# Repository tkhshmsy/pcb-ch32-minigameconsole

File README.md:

# PCB-ch32-minigameconsole

Private designed PCB for [CH32V003-GameConsole](https://github.com/wagiminator/CH32V003-GameConsole)

## Features
* Size 45 x 48 mm
  * Panelized 4 pcs in 100 x 100mm
* Using THT parts except CH32V003
  * All parts are able to purchase from [Akizuki-Denshi](https://akizukidenshi.com/)

## Schematic and Layout

## BOM
|Ref|Name|Qty|Description|Link|
|---|----|---|-----------|----|
|U1|CH32V003J4M6|1||https://akizukidenshi.com/catalog/g/g118062/|
|U1 ext|SOP8 to DIP8 conversion board|1||https://akizukidenshi.com/catalog/g/g105154|
|U2|OLED 0.96inch|1|128x64 monochrome, i2c|https://akizukidenshi.com/catalog/g/g112031/|
|BT1|CR2032 holder|1||https://akizukidenshi.com/catalog/g/g100706/|
|Q1|2SA1015|1||https://akizukidenshi.com/catalog/g/g117091/|
|LS1|Sounder/Speaker|1||https://akizukidenshi.com/catalog/g/g104118/|
|C1|Capacitor 0.1uF|1||https://akizukidenshi.com/catalog/g/g115927/|
|C2|Capacitor 10uF|1||https://akizukidenshi.com/catalog/g/g103095/|
|R1|Resist 8k2|1||https://akizukidenshi.com/catalog/g/g116822/|
|R2|Resist 3k9|1||https://akizukidenshi.com/catalog/g/g116392/|
|R3|Resist 20k|1|for test build, use 22k|https://akizukidenshi.com/catalog/g/g107842/ or https://akizukidenshi.com/catalog/g/g116223/|
|R4, R7|Resist 2k|2||https://akizukidenshi.com/catalog/g/g116202/|
|R5, R6|Resist 0|2|These are 'Dummy' to create resistance value of R1 / R2 in combination. See 'Other set of resistors'||
|R8|Resist 1k|1|see Errata|https://akizukidenshi.com/catalog/g/g116102/|
|SW1|Slide switch|1||https://akizukidenshi.com/catalog/g/g115707/|
|SW2-6|Push switch|5||https://akizukidenshi.com/catalog/g/g103647/|
|J1|3 pins header/socket|1|SWD port|https://akizukidenshi.com/catalog/g/g115510/ or https://akizukidenshi.com/catalog/g/g110098/|
|--|WCH-LinkE emulator|1|SWD/JTAG tool|https://akizukidenshi.com/catalog/g/g118065/|

### Other set of resistors

|Ref|Set 1(Original)|Set 2|
|---|---------------|-----|
|R1|8k2|4k7|
|R2|3k9|2k2|
|R3|20k|22k|
|R4|2k|2k2|
|R5|0|4k7|
|R6|0|2k2|
|R7|2k|2k2|
|R8|1k|100|

## Errata
* v0.1
  * Sometimes, The LEFT button (SW5) acts as the RIGHT button.
    * It seems to be due to poor analog wiring.
  * Sound too small
    * It seems the limiting resist (R8=1k) is too large.

## How to run
on Linux,

1. Prepare
   1. Get [WCH-LinkE](https://akizukidenshi.com/catalog/g/g118065/)
   2. Download original repository https://github.com/wagiminator/CH32V003-GameConsole
      1. use *.bin files.
   3. Download repository https://github.com/cnlohr/ch32v003fun
      1. use the tool 'minichlink' to write firmware.
2. Write firmware
   1. Build 'minichlink'
   2. Connect WCH-LinkE to PC and PCB with pushing 'ModeS' button.
      1. ref: https://github.com/cnlohr/ch32v003fun/issues/227
      2. to PCB side, connect '3V3, 'GND' and 'SWDIO' to J1.
   3. Write firmware
        ```bash
        ## e.g. tiny-tris
        $ ./minichlink -w CH32V003-GameConsole/software/tiny_tris/tiny_tris.bin flash -b
        ```
3. Enjoy !

## License
Original codes are licensed under Creative Commons.
* Creative Commons Attribution-ShareAlike 3.0 Unported License. (http://creativecommons.org/licenses/by-sa/3.0/)

This PCB project is licensed under same Creative Commons too.

## Author
* tkhshmsy@gmail.com

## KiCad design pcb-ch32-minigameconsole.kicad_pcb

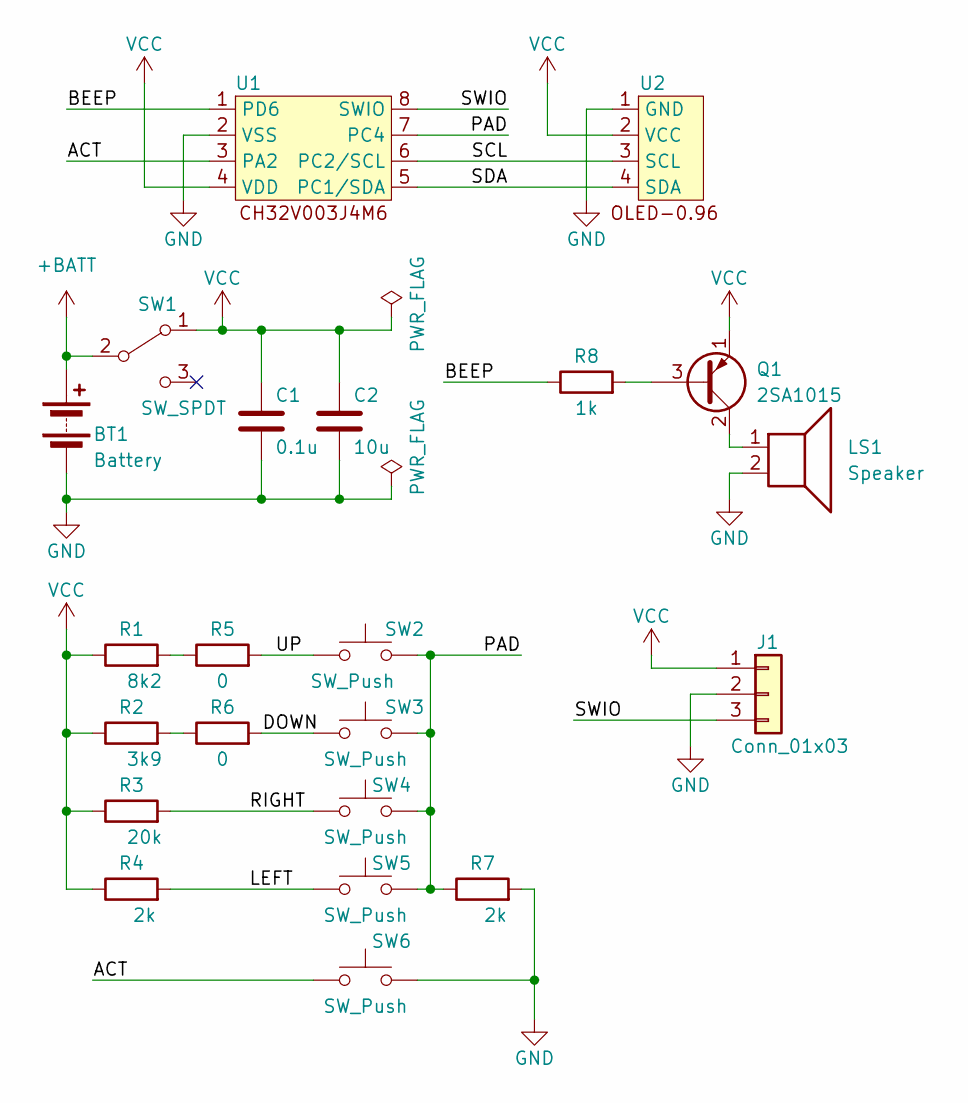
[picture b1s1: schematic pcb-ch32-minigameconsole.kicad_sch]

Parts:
BT1: Battery; CH25-2032LF
C1: 0.1u; C_Disc_D4.7mm_W2.5mm_P5.00mm
C2: 10u; C_Disc_D4.7mm_W2.5mm_P5.00mm
J1: Conn_01x03; PinSocket_1x03_P2.54mm_Horizontal
LS1: Speaker; PKM13EPYH4000-A0
Q1: 2SA1015; TO-92_Inline
R1: 8k2; R_Axial_DIN0204_L3.6mm_D1.6mm_P5.08mm_Horizontal
R2: 3k9; R_Axial_DIN0204_L3.6mm_D1.6mm_P5.08mm_Horizontal
R3: 20k; R_Axial_DIN0204_L3.6mm_D1.6mm_P5.08mm_Horizontal
R4, R7: 2k; R_Axial_DIN0204_L3.6mm_D1.6mm_P5.08mm_Horizontal
R5, R6: 0; R_Axial_DIN0204_L3.6mm_D1.6mm_P5.08mm_Horizontal
R8: 1k; R_Axial_DIN0204_L3.6mm_D1.6mm_P5.08mm_Horizontal
SW1: SW_SPDT; SS-12D00G3
SW2, SW3, SW4, SW5, SW6: SW_Push; SW_PUSH_6mm_H7.3mm
U1: CH32V003J4M6-Dual
U2: OLED-0.96

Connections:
+BATT: BT1.1 (+), SW1.2 (B)
/ACT: SW6.1, U1.3 (PA2)
/BEEP: R8.1, U1.1 (PD6)
/DOWN: R6.2, SW3.1
/LEFT: R4.2, SW5.1
/PAD: R7.1, SW2.2, SW3.2, SW4.2, SW5.2, U1.7 (PC4)
/RIGHT: R3.2, SW4.1
/SCL: U1.6 (PC2/SCL), U2.3 (SCL)
/SDA: U1.5 (PC1/SDA), U2.4 (SDA)
/SWIO: J1.3, U1.8 (SWIO)
/UP: R5.2, SW2.1
GND: BT1.2 (-), C1.2, C2.2, J1.2, LS1.2, R7.2, SW6.2, U1.2 (VSS), U2.1 (GND)
unnamed: Q1.3 (B), R8.2
unnamed: LS1.1, Q1.2 (C)
unnamed: R1.2, R5.1
unnamed: R2.2, R6.1
VCC: C1.1, C2.1, J1.1, Q1.1 (E), R1.1, R2.1, R3.1, R4.1, SW1.1 (A), U1.4 (VDD), U2.2 (VCC)

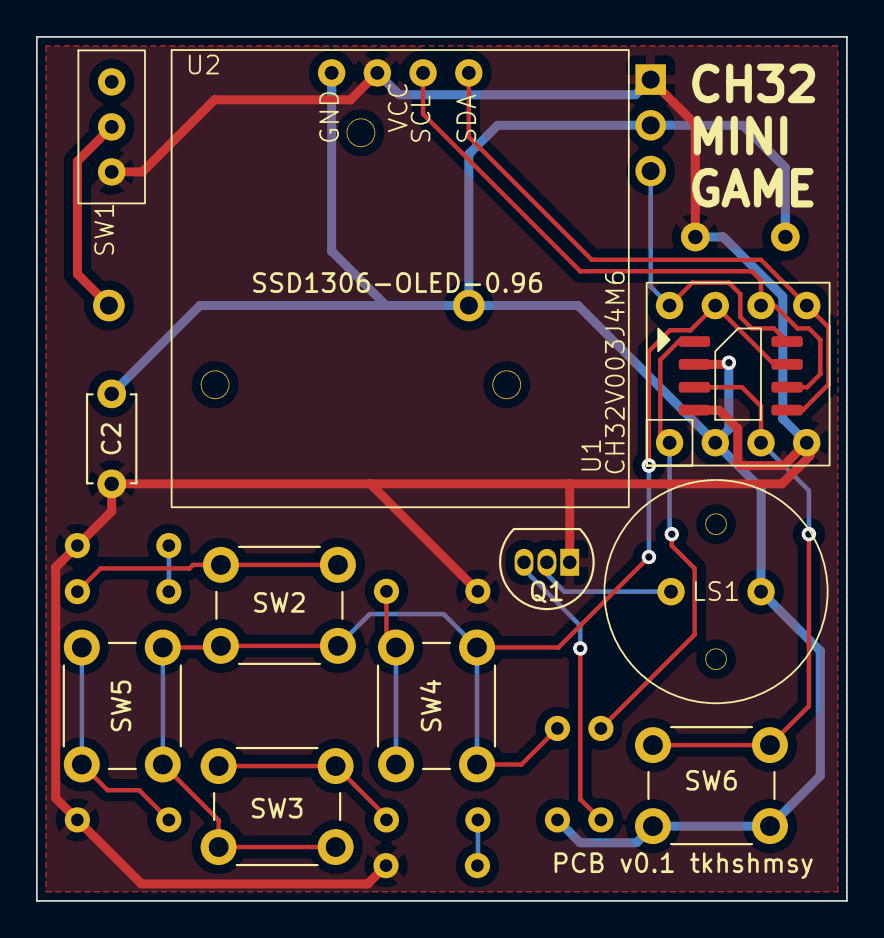
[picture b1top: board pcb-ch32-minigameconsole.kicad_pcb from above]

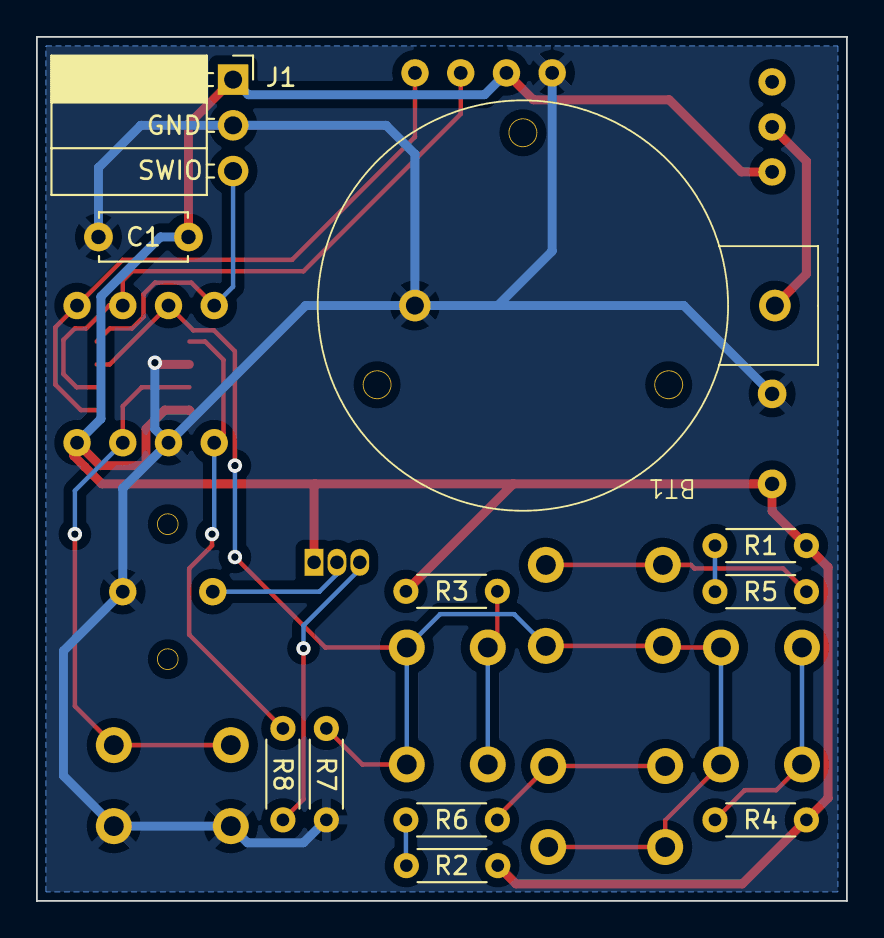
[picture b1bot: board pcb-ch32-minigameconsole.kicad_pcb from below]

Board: 2 copper layers, 45.0 x 48.0 mm, 22 parts (11 on the bottom side), 17 nets.

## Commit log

2024-01-29 panelized
2024-01-29 Add README
2024-02-15 Fix README
2024-02-21 Fix README about using resistors
